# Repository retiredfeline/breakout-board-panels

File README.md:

# Breakout board panels

I imported some breakout boards at [Kevin Neubaur DIP-Breakout-Boards](https://github.com/neubauek/DIP-Breakout-Boards) from Eagle format into Kicad 5.1 and panelised them using [Kicad Panelizer](https://github.com/sej7278/kicad-panelizer) so that you can get them manufactured cheaply. The manufacturer may charge extra for V-cuts so check as this may affect the economics.

A description of this project can be found at [Hackaday](https://hackaday.io/project/172085-breakout-board-panels).

Feel free to use the Kicad or Gerber files here under [CC-by-SA 4.0](https://creativecommons.org/licenses/by-sa/4.0/). I will add to the collection of converted boards with time.

## Original text in the files and libraries this is derived from: SparkFun-Aesthetics, SparkFun-Connectors, and Kevin-GenericICFootprints

We've spent an enormous amount of time creating and checking these footprints and parts, but it is the end user's responsibility to ensure correctness and suitablity for a given componet or application. If you enjoy using this library, please buy one of our products at www.sparkfun.com.

[Creative Commons ShareAlike 4.0 International](https://creativecommons.org/licenses/by-sa/4.0/)

You are welcome to use this library for commercial purposes. For attribution, we ask that when you begin to sell your device using our footprint, you email us with a link to the product being sold. We want bragging rights that we helped (in a very small part) to create your 8th world wonder. We would like the opportunity to feature your device on our homepage.

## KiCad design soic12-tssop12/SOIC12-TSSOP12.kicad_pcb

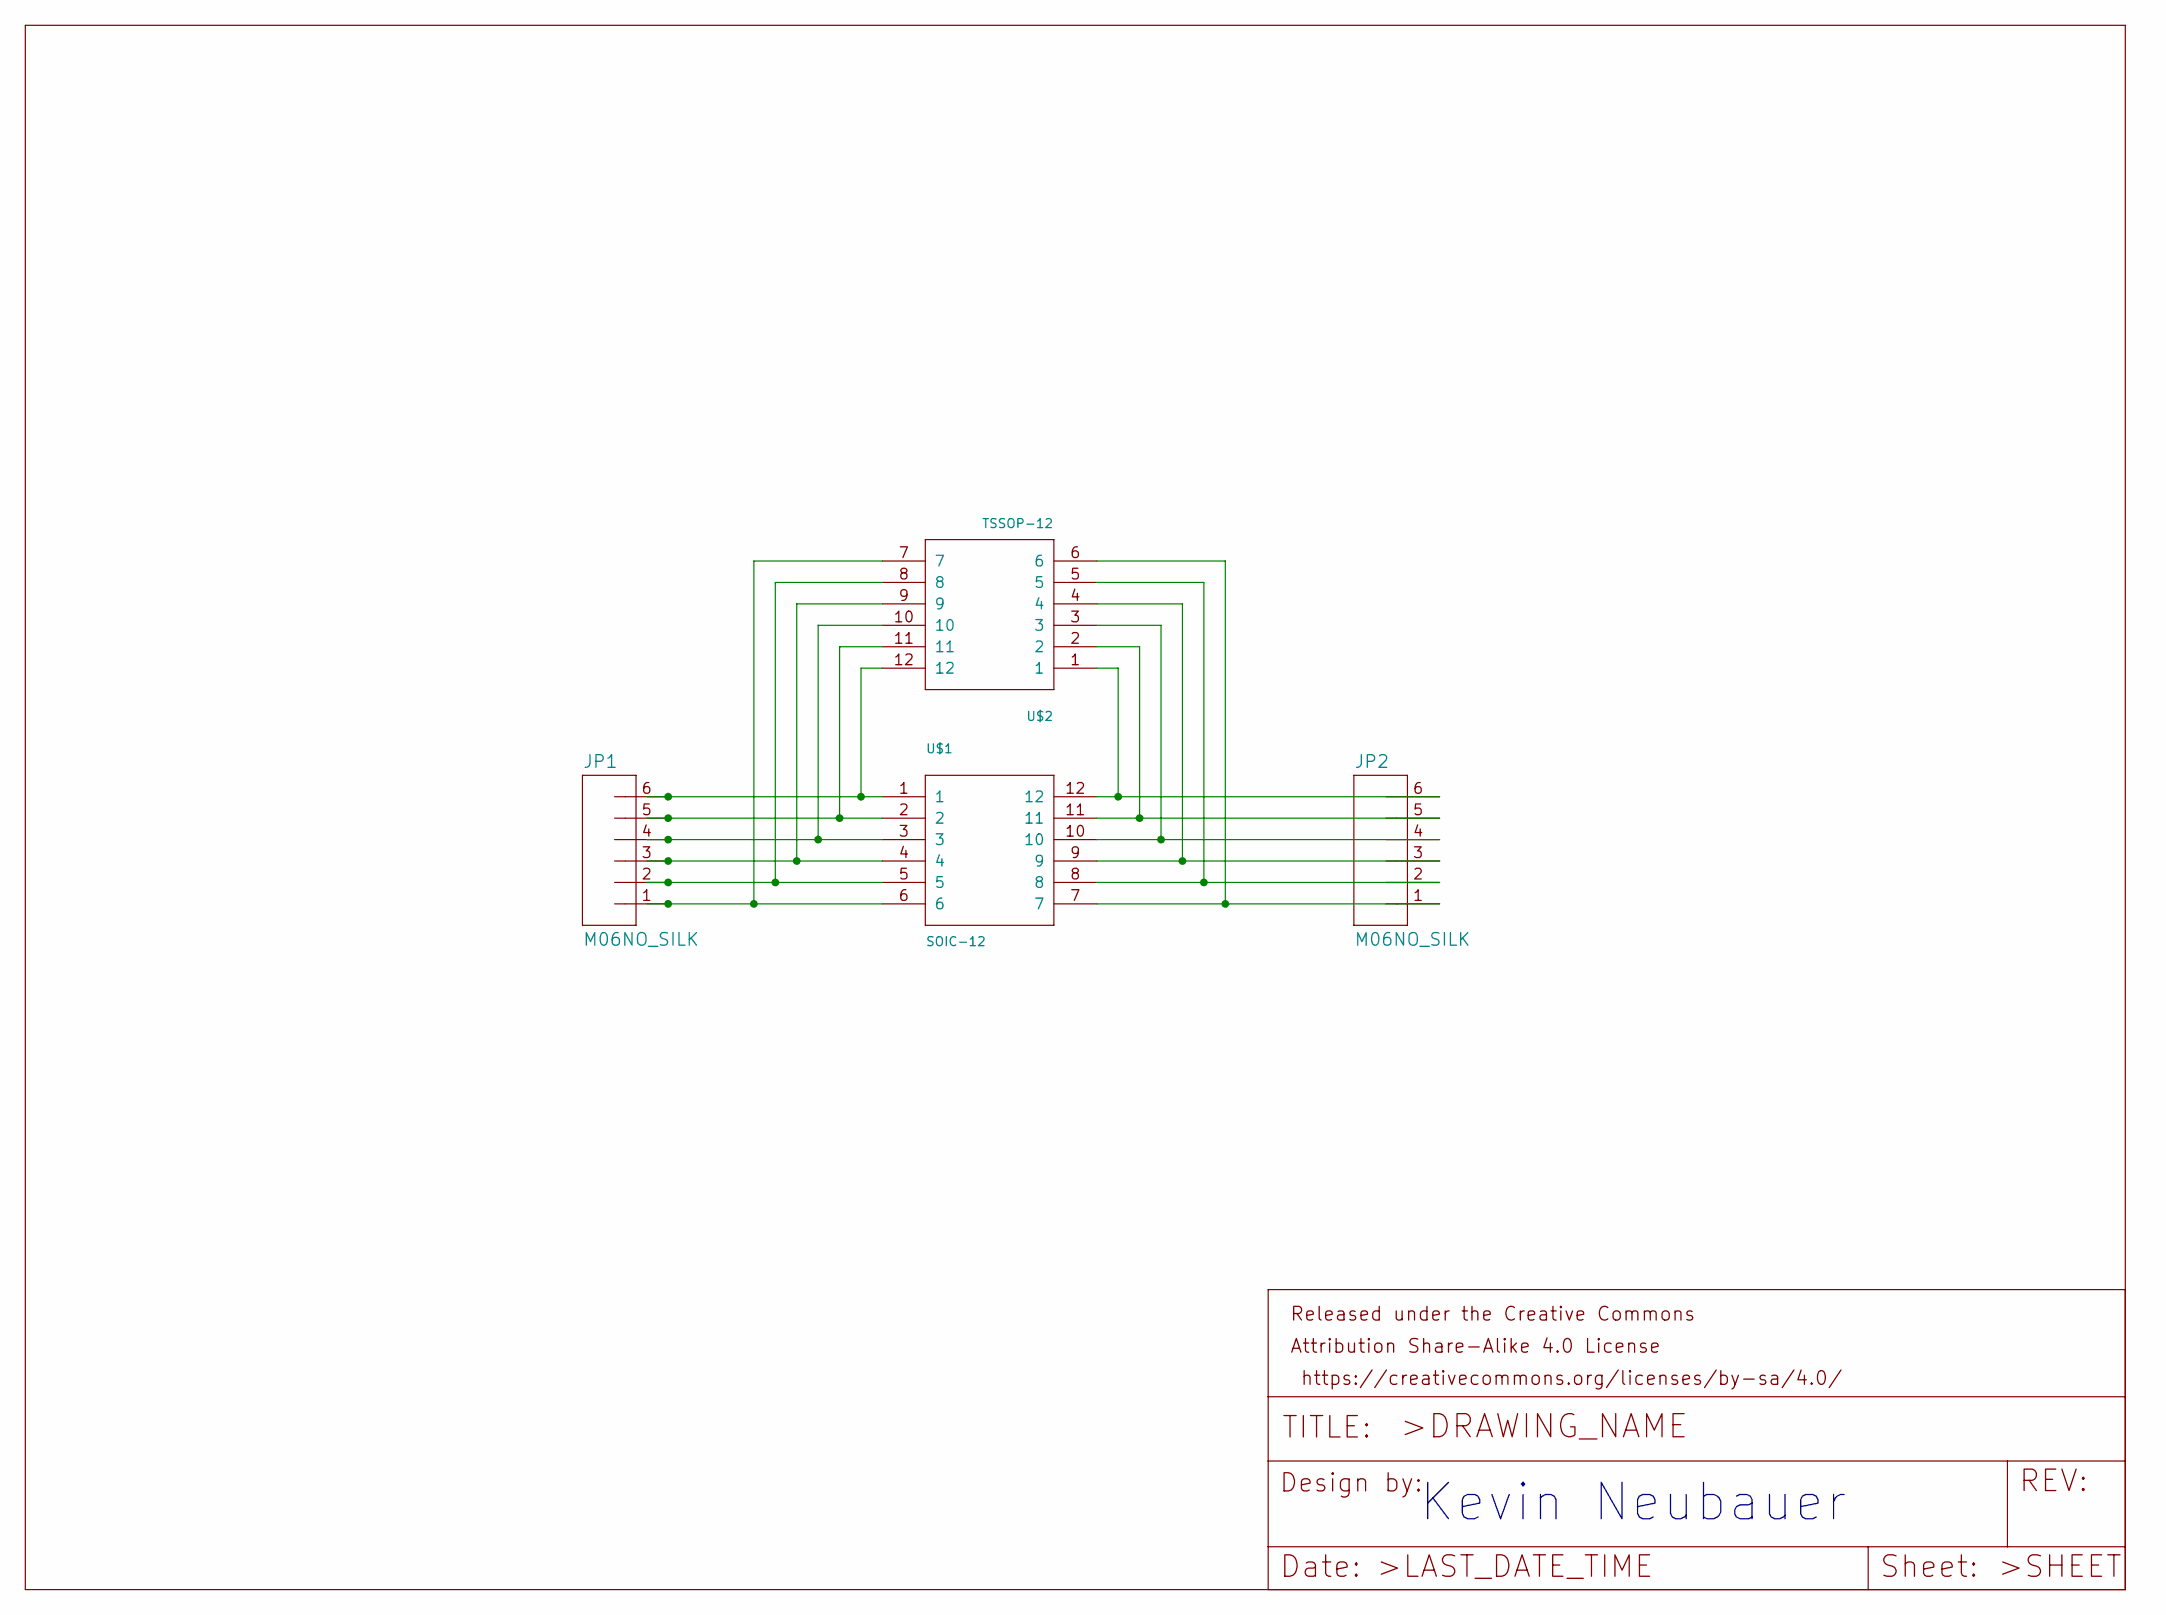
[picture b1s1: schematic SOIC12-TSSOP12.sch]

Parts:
FRAME1: FRAME-LETTER; CREATIVE_COMMONS
JP1, JP2: M06NO_SILK; 1X06_NO_SILK
U$1: SOIC-12
U$2: TSSOP-12; TSSOP12

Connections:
unnamed: JP1.1, U$1.6, U$2.7
unnamed: JP1.2, U$1.5, U$2.8
unnamed: JP1.3, U$1.4, U$2.9
unnamed: JP1.4, U$1.3, U$2.10
unnamed: JP1.5, U$1.2, U$2.11
unnamed: JP1.6, U$1.1, U$2.12
unnamed: JP2.1, U$1.7, U$2.6
unnamed: JP2.2, U$1.8, U$2.5
unnamed: JP2.3, U$1.9, U$2.4
unnamed: JP2.4, U$1.10, U$2.3
unnamed: JP2.5, U$1.11, U$2.2
unnamed: JP2.6, U$1.12, U$2.1

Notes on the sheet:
Kevin Neubauer

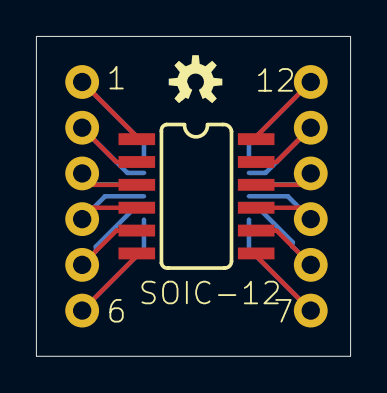
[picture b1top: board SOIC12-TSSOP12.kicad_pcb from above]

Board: 2 copper layers, 17.4 x 17.8 mm, 7 parts (0 on the bottom side), 12 nets.

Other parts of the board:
U$3, U$4: OSHW-LOGO-S

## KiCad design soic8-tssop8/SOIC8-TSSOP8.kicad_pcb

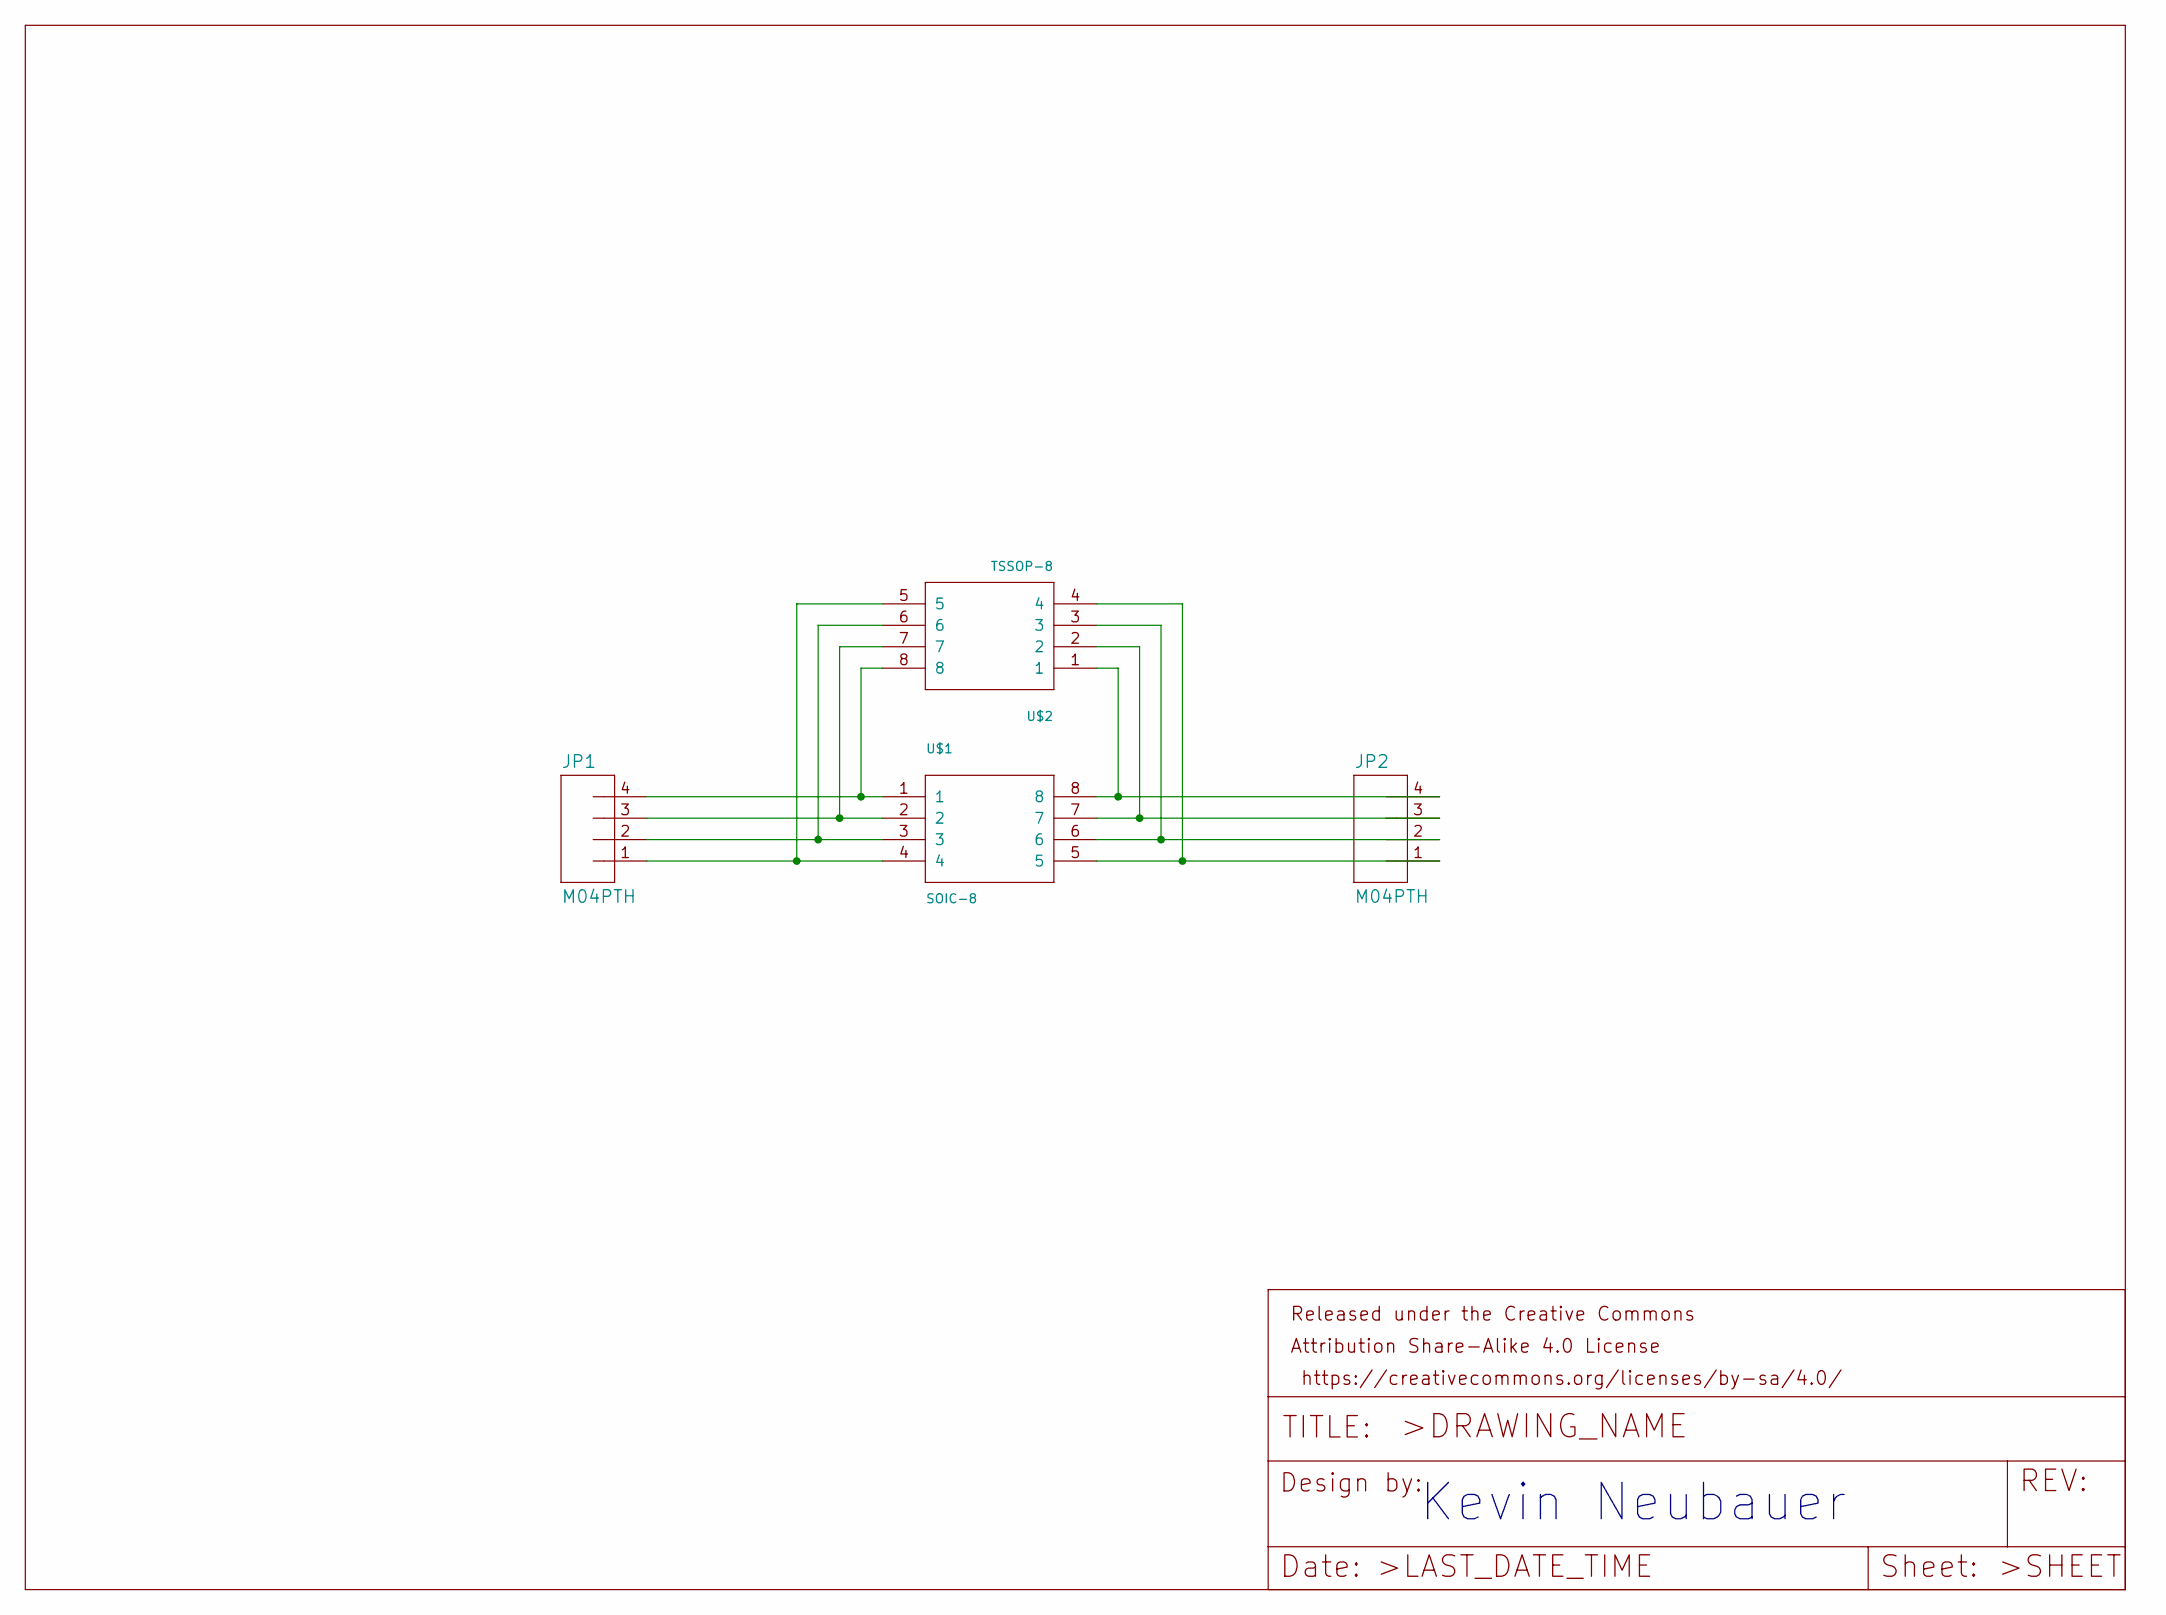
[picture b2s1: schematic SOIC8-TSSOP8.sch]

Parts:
FRAME1: FRAME-LETTER; CREATIVE_COMMONS
JP1, JP2: M04PTH; 1X04
U$1: SOIC-8
U$2: TSSOP-8; TSSOP8

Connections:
unnamed: JP1.1, U$1.4, U$2.5
unnamed: JP1.2, U$1.3, U$2.6
unnamed: JP1.3, U$1.2, U$2.7
unnamed: JP1.4, U$1.1, U$2.8
unnamed: JP2.1, U$1.5, U$2.4
unnamed: JP2.2, U$1.6, U$2.3
unnamed: JP2.3, U$1.7, U$2.2
unnamed: JP2.4, U$1.8, U$2.1

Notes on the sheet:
Kevin Neubauer

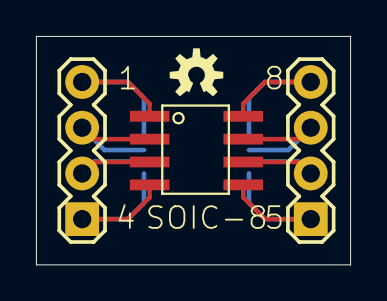
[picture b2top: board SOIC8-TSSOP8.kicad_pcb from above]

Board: 2 copper layers, 17.4 x 12.7 mm, 7 parts (0 on the bottom side), 8 nets.

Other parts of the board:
U$3, U$4: OSHW-LOGO-S

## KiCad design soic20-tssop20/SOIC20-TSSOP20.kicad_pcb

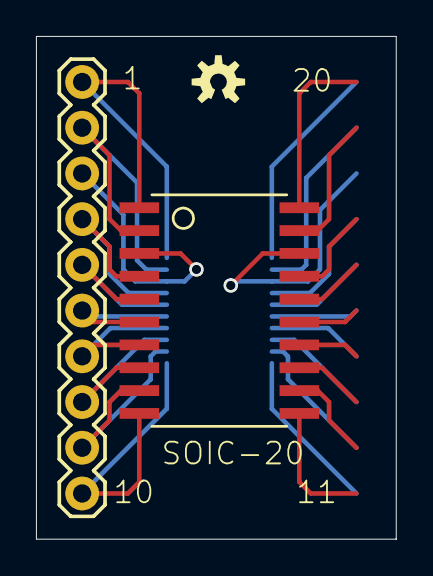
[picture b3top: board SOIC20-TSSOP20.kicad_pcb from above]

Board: 2 copper layers, 20.0 x 27.9 mm, 6 parts (0 on the bottom side), 20 nets.

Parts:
FRAME1: FRAME-LETTER; CREATIVE_COMMONS
JP1: M10; 1X10
U$1: SOIC-20
U$2: TSSOP-20; TSSOP20
U$3, U$4: OSHW-LOGO-S

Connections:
unnamed: U$1.10, U$2.11
unnamed: U$1.9, U$2.12
unnamed: U$1.8, U$2.13
unnamed: U$1.7, U$2.14
unnamed: U$1.6, U$2.15
unnamed: U$1.5, U$2.16
unnamed: U$1.4, U$2.17
unnamed: U$1.3, U$2.18
unnamed: U$1.2, U$2.19
unnamed: U$1.1, U$2.20
unnamed: JP1.1, U$1.11, U$2.10
unnamed: JP1.2, U$1.12, U$2.9
unnamed: JP1.3, U$1.13, U$2.8
unnamed: JP1.4, U$1.14, U$2.7
unnamed: JP1.5, U$1.15, U$2.6
unnamed: JP1.6, U$1.16, U$2.5
unnamed: JP1.7, U$1.17, U$2.4
unnamed: JP1.8, U$1.18, U$2.3
unnamed: JP1.9, U$1.19, U$2.2
unnamed: JP1.10, U$1.20, U$2.1

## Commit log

2020-06-01 Initial release
2020-06-01 Fix up hyperlink to Hackaday project
2020-11-27 Remove fp-info-cache files

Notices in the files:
parts and their libraries:
Released under the Creative Commons Attribution Share-Alike 4.0 License
